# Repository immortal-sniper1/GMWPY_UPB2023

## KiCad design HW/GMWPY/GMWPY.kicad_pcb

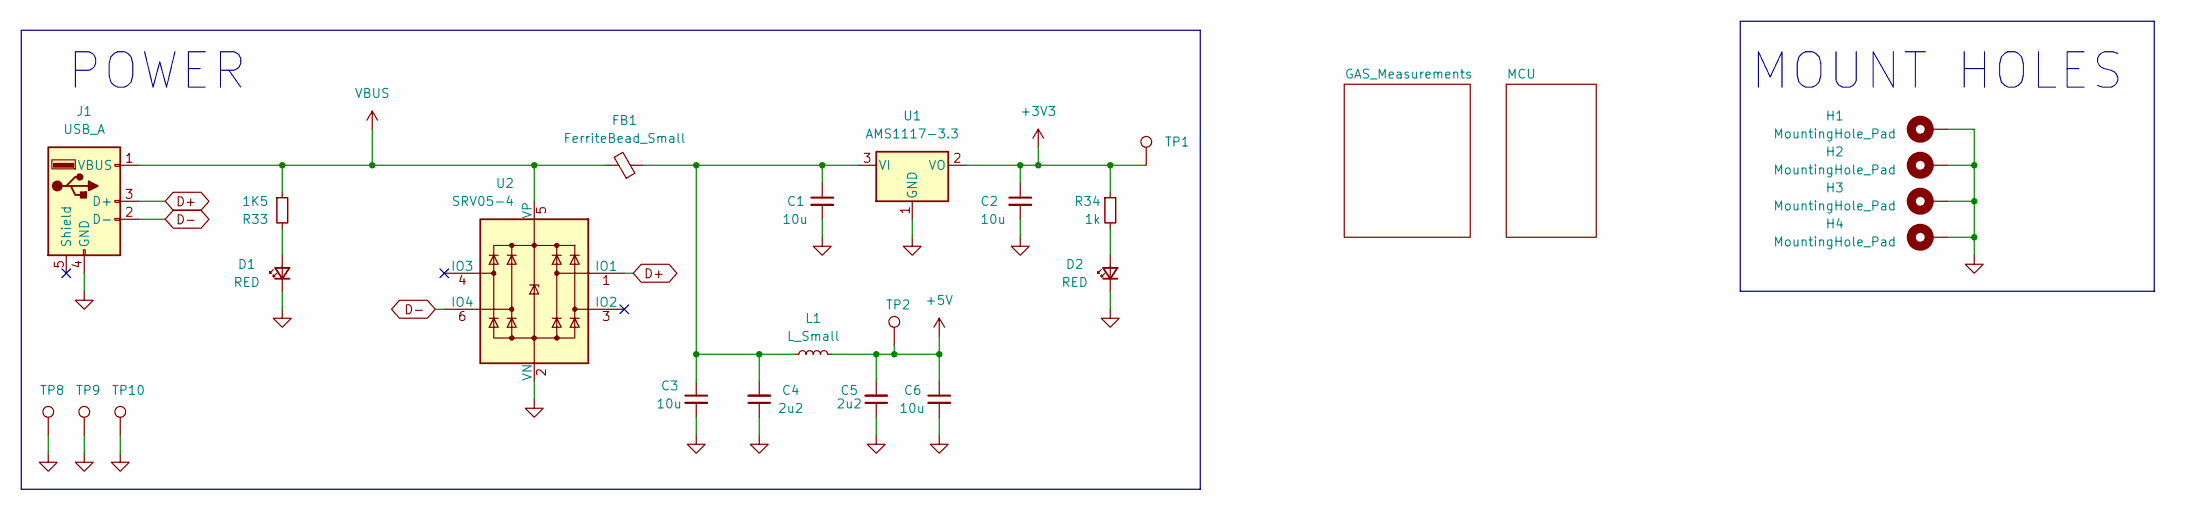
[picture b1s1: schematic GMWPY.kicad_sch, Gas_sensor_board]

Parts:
C1, C2, C3, C6: 10u; C_0805_2012Metric; LCSC C15850
C4, C5: 2u2; C_0603_1608Metric; LCSC C23630
D1, D2: RED; LED_0603_1608Metric; LCSC C2286
FB1: FerriteBead_Small; L_0805_2012Metric; LCSC C1015
H1, H2, H3, H4: MountingHole_Pad; MountingHole_3.2mm_M3_DIN965_Pad_TopBottom
J1: USB_A; USB1040GFLB
L1: L_Small; L_0603_1608Metric; LCSC C13415
R33: 1K5; R_0603_1608Metric; LCSC C22843
R34: 1k; R_0603_1608Metric; LCSC C21190
TP1, TP2, TP8, TP9, TP10: TestPoint; TestPoint_Pad_1.5x1.5mm
U1: AMS1117-3.3; SOT-223-3_TabPin2; LCSC C6186
U2: SRV05-4; SOT-23-6; LCSC C85364

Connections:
+3V3: C2.1, R34.1, TP1.1, U1.2 (VO); also elsewhere on the board
+5V: C5.2, C6.1, L1.2, TP2.1; also elsewhere on the board
D+: J1.3 (D+), U2.1 (IO1); also elsewhere on the board
D-: J1.2 (D-), U2.6 (IO4); also elsewhere on the board
GND: C1.2, C2.2, C3.2, C4.1, C5.1, C6.2, D1.1 (K), D2.1 (K), H1.1, H2.1, H3.1, H4.1, J1.4 (GND), TP8.1, TP9.1, TP10.1, U1.1 (GND), U2.2 (VN); also elsewhere on the board
unnamed: C1.1, C3.1, C4.2, FB1.1, L1.1, U1.3 (VI)
unnamed: D1.2 (A), R33.2
unnamed: D2.2 (A), R34.2
VBUS: FB1.2, J1.1 (VBUS), R33.1, U2.5 (VP); also elsewhere on the board

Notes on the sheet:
POWER
MOUNT HOLES

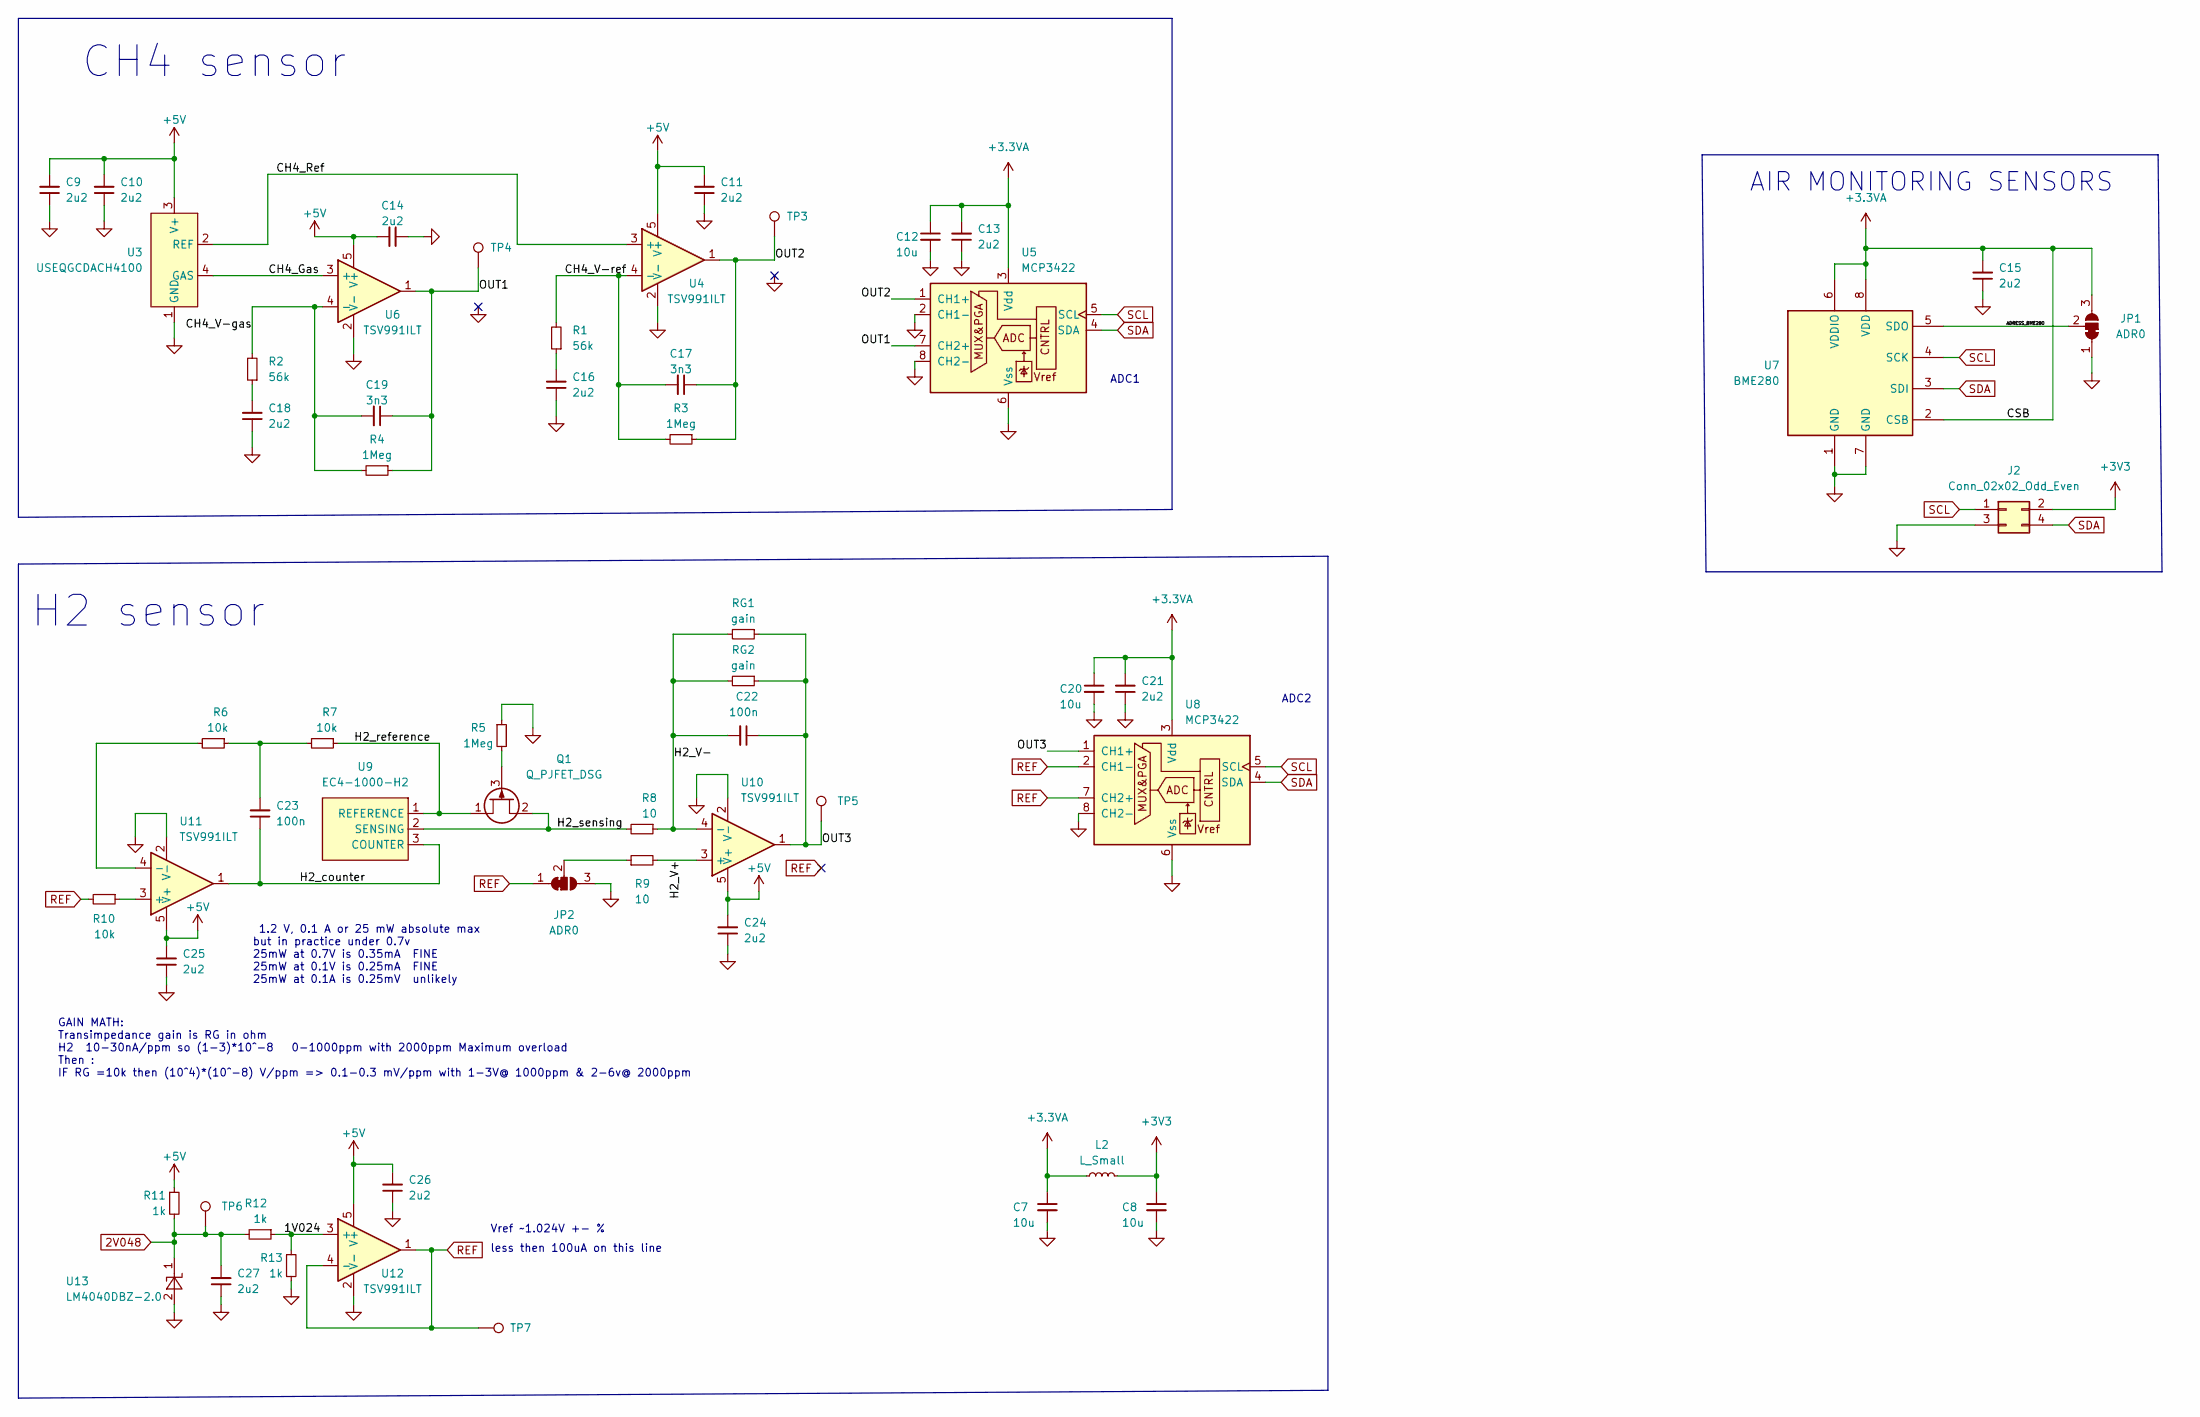
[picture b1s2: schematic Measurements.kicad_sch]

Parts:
C7, C8, C12, C20: 10u; C_0805_2012Metric; LCSC C15850
C9, C10, C11, C13, C14, C15, C16, C18, C21, C24, C25, C26, C27: 2u2; C_0603_1608Metric; LCSC C23630
C17, C19: 3n3; C_0603_1608Metric; LCSC C1613
C22, C23: 100n; C_0603_1608Metric; LCSC C14663
J2: Conn_02x02_Odd_Even; PinHeader_2x02_P2.54mm_Vertical
JP1, JP2: ADR0; SolderJumper-3_P1.3mm_Bridged12_RoundedPad1.0x1.5mm_NumberL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
L2: L_Small; L_0603_1608Metric; LCSC C13415
Q1: Q_PJFET_DSG; SOT-23; LCSC C106763
R1, R2: 56k; R_0603_1608Metric; LCSC C23206
R3, R4, R5: 1Meg; R_0603_1608Metric; LCSC C22935
R6, R7, R10: 10k; R_0603_1608Metric; LCSC C25804
R8, R9: 10; R_0603_1608Metric; LCSC C22859
R11, R12, R13: 1k; R_0603_1608Metric; LCSC C21190
RG1: gain; R_0603_1608Metric; LCSC x
RG2: gain; R_0603_1608Metric; LCSC C25804
TP3, TP4, TP5, TP6, TP7: TestPoint; TestPoint_Pad_1.5x1.5mm
U3: USEQGCDACH4100; KEMET-4-PIN-GAS-SENSOR; MOUSER 80-USEQGCDACH4100
U4, U6, U10, U11, U12: TSV991ILT; SOT-23-5_HandSoldering; LCSC C157443
U5, U8: MCP3422; SOIC-8_3.9x4.9mm_P1.27mm
U7: BME280; Bosch_LGA-8_2.5x2.5mm_P0.65mm_ClockwisePinNumbering
U9: EC4-1000-H2; EC4-3pin; MOUSER 523-EC4-1000-H2
U13: LM4040DBZ-2.0; SOT-23; LCSC C431732

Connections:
2V048: C27.2, R11.2, R12.2, TP6.1, U13.1 (K)
+3.3VA: C7.1, C12.1, C13.2, C15.2, C20.1, C21.2, JP1.3 (B), L2.1, U5.3 (Vdd), U7.2 (CSB), U7.6 (VDDIO), U7.8 (VDD), U8.3 (Vdd)
+3V3: C8.1, J2.2, L2.2; also elsewhere on the board
+5V: C9.2, C10.2, C11.2, C14.2, C24.2, C25.2, C26.2, R11.1, U3.3 (V+), U4.5 (V+), U6.5 (V+), U10.5 (V+), U11.5 (V+), U12.5 (V+); also elsewhere on the board
/GAS_Measurements/1V024: R12.1, R13.1, U12.3 (+)
/GAS_Measurements/ADRESS_BME280: JP1.2 (C), U7.5 (SDO)
/GAS_Measurements/CH4_Gas: U3.4 (GAS), U6.3 (+)
/GAS_Measurements/CH4_Ref: U3.2 (REF), U4.3 (+)
/GAS_Measurements/CH4_V-gas: C19.2, R2.2, R4.2, U6.4 (-)
/GAS_Measurements/CH4_V-ref: C17.2, R1.2, R3.2, U4.4 (-)
/GAS_Measurements/H2_V+: R9.2, U10.3 (+)
/GAS_Measurements/H2_V-: C22.2, R8.1, RG1.2, RG2.2, U10.4 (-)
/GAS_Measurements/H2_counter: C23.1, U9.3 (COUNTER), U11.1
/GAS_Measurements/H2_reference: Q1.1 (D), R7.1, U9.1 (REFERENCE)
/GAS_Measurements/H2_sensing: Q1.2 (S), R8.2, U9.2 (SENSING)
/GAS_Measurements/OUT1: C19.1, R4.1, TP4.1, U5.7 (CH2+), U6.1
/GAS_Measurements/OUT2: C17.1, R3.1, TP3.1, U4.1, U5.1 (CH1+)
/GAS_Measurements/OUT3: C22.1, RG1.1, RG2.1, TP5.1, U8.1 (CH1+), U10.1
GND: C7.2, C8.2, C9.1, C10.1, C11.1, C12.2, C13.1, C14.1, C15.1, C16.1, C18.1, C20.2, C21.1, C24.1, C25.1, C26.1, C27.1, J2.3, JP1.1 (A), JP2.3 (B), R5.1, R13.2, U3.1 (GND), U4.2 (V-), U5.2 (CH1-), U5.6 (Vss), U5.8 (CH2-), U6.2 (V-), U7.1 (GND), U7.7 (GND), U8.6 (Vss), U8.8 (CH2-), U10.2 (V-), U11.2 (V-), U12.2 (V-), U13.2 (A); also elsewhere on the board
GPIO_5: J2.1, U5.5 (SCL), U7.4 (SCK), U8.5 (SCL); also elsewhere on the board
GPIO_6: J2.4, U5.4 (SDA), U7.3 (SDI), U8.4 (SDA); also elsewhere on the board
unnamed: C16.2, R1.1
unnamed: C18.2, R2.1
unnamed: C23.2, R6.1, R7.2
unnamed: JP2.2 (C), R9.1
unnamed: Q1.3 (G), R5.2
unnamed: R6.2, U11.4 (-)
unnamed: R10.1, U11.3 (+)
REF: JP2.1 (A), R10.2, TP7.1, U8.2 (CH1-), U8.7 (CH2+), U12.1, U12.4 (-)

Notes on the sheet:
GAIN MATH: Transimpedance gain is RG in ohm H2 10-30nA/ppm so (1-3)*10^-8 0-1000ppm with 2000ppm Maximum overload Then : IF RG =10k then (10^4)*(10^-8) V/ppm => 0.1-0.3 mV/ppm with 1-3V@ 1000ppm & 2-6v@ 2000ppm
Vref ~1.024V +- %
AIR MONITORING SENSORS
ADC1
less then 100uA on this line
CH4 sensor
1.2 V, 0.1 A or 25 mW absolute max but in practice under 0.7v 25mW at 0.7V is 0.35mA FINE 25mW at 0.1V is 0.25mA FINE 25mW at 0.1A is 0.25mV unlikely
H2 sensor
ADC2

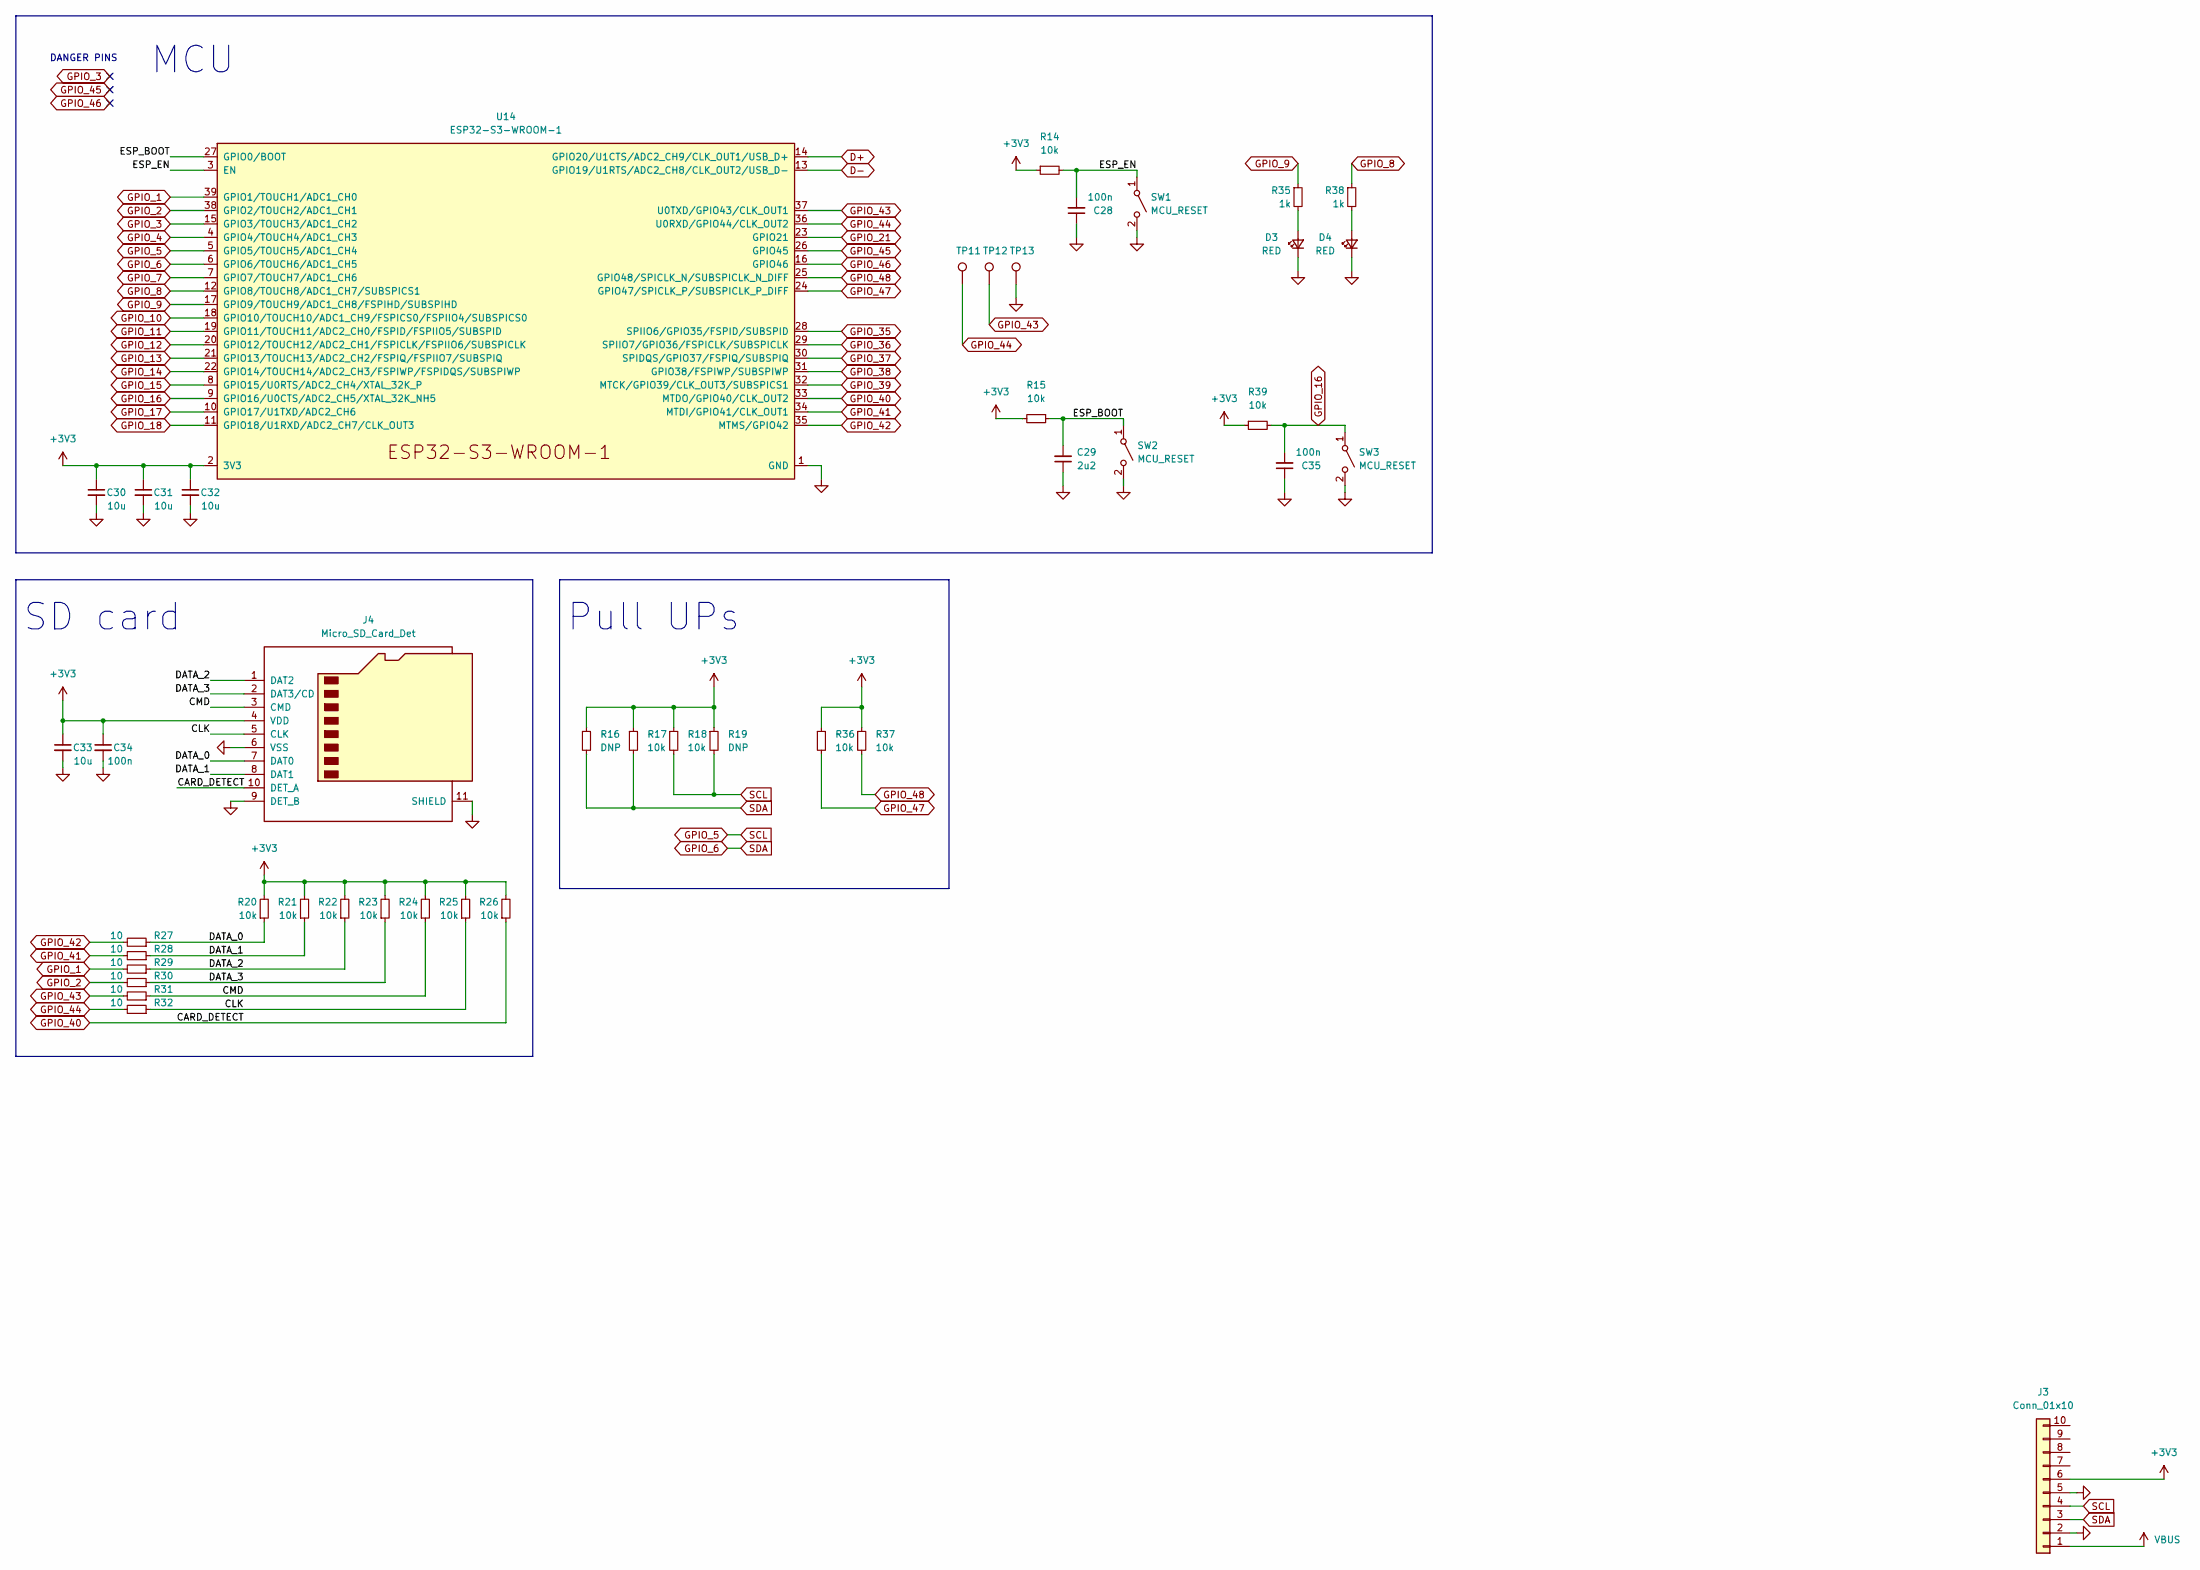
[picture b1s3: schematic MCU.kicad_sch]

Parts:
C28, C34, C35: 100n; C_0603_1608Metric_Pad1.08x0.95mm_HandSolder; LCSC C14663
C29: 2u2; C_0603_1608Metric; LCSC C23630
C30, C31, C32, C33: 10u; C_0805_2012Metric; LCSC C15850
D3, D4: RED; LED_0603_1608Metric; LCSC C2286
J3: Conn_01x10; PinHeader_1x06_P2.54mm_Vertical
J4: Micro_SD_Card_Det; microSD_HC_Molex_104031-0811; LCSC C585350
R14, R15, R17, R18, R36, R37, R39: 10k; R_0603_1608Metric_Pad0.98x0.95mm_HandSolder; LCSC C25804
R16, R19: DNP; R_0603_1608Metric_Pad0.98x0.95mm_HandSolder
R20, R21, R22, R23, R24, R25, R26: 10k; R_0402_1005Metric; LCSC C25744
R27, R28, R29, R30, R31, R32: 10; R_0402_1005Metric; LCSC C25077
R35, R38: 1k; R_0603_1608Metric; LCSC C21190
SW1, SW2, SW3: MCU_RESET; PTS526SK15SMTR2LFS; LCSC C318884
TP11, TP12, TP13: TestPoint; TestPoint_Pad_1.5x1.5mm
U14: ESP32-S3-WROOM-1; LCSC C2913204

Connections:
+3V3: C30.1, C31.1, C32.1, C33.1, C34.1, J3.6, J4.4 (VDD), R14.1, R15.2, R16.1, R17.1, R18.1, R19.1, R20.2, R21.2, R22.2, R23.2, R24.2, R25.2, R26.2, R36.1, R37.1, R39.1, U14.2 (3V3); also elsewhere on the board
/MCU/CLK: J4.5 (CLK), R25.1, R32.1
/MCU/CMD: J4.3 (CMD), R24.1, R31.1
/MCU/DATA_0: J4.7 (DAT0), R20.1, R27.1
/MCU/DATA_1: J4.8 (DAT1), R21.1, R28.1
/MCU/DATA_2: J4.1 (DAT2), R22.1, R29.1
/MCU/DATA_3: J4.2 (DAT3/CD), R23.1, R30.1
/MCU/ESP_BOOT: C29.2, R15.1, SW2.1 (A), U14.27 (GPIO0/BOOT)
/MCU/ESP_EN: C28.2, R14.2, SW1.1 (A), U14.3 (EN)
D+: U14.14 (GPIO20/U1CTS/ADC2_CH9/CLK_OUT1/USB_D+); also elsewhere on the board
D-: U14.13 (GPIO19/U1RTS/ADC2_CH8/CLK_OUT2/USB_D-); also elsewhere on the board
GND: C28.1, C29.1, C30.2, C31.2, C32.2, C33.2, C34.2, C35.1, D3.1 (K), D4.1 (K), J3.2, J3.5, J4.6 (VSS), J4.9 (DET_B), J4.11 (SHIELD), SW1.2 (B), SW2.2 (B), SW3.2 (B), TP13.1, U14.1 (GND), U14.40 (GND), U14.41 (GND); also elsewhere on the board
GPIO_1: R29.2, U14.39 (GPIO1/TOUCH1/ADC1_CH0)
GPIO_2: R30.2, U14.38 (GPIO2/TOUCH2/ADC1_CH1)
GPIO_3: U14.15 (GPIO3/TOUCH3/ADC1_CH2)
GPIO_4: U14.4 (GPIO4/TOUCH4/ADC1_CH3)
GPIO_5: J3.4, R18.2, R19.2, U14.5 (GPIO5/TOUCH5/ADC1_CH4); also elsewhere on the board
GPIO_6: J3.3, R16.2, R17.2, U14.6 (GPIO6/TOUCH6/ADC1_CH5); also elsewhere on the board
GPIO_7: U14.7 (GPIO7/TOUCH7/ADC1_CH6)
GPIO_8: R38.1, U14.12 (GPIO8/TOUCH8/ADC1_CH7/SUBSPICS1)
GPIO_9: R35.1, U14.17 (GPIO9/TOUCH9/ADC1_CH8/FSPIHD/SUBSPIHD)
GPIO_10: U14.18 (GPIO10/TOUCH10/ADC1_CH9/FSPICS0/FSPIIO4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)
GPIO_11: U14.19 (GPIO11/TOUCH11/ADC2_CH0/FSPID/FSPIIO5/S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)
GPIO_12: U14.20 (GPIO12/TOUCH12/ADC2_CH1/FSPICLK/FSPIIO6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)
GPIO_13: U14.21 (GPIO13/TOUCH13/ADC2_CH2/FSPIQ/FSPIIO7/S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)
GPIO_14: U14.22 (GPIO14/TOUCH14/ADC2_CH3/FSPIWP/FSPIDQS/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)
GPIO_15: U14.8 (GPIO15/U0RTS/ADC2_CH4/XTAL_32K_P)
GPIO_16: C35.2, R39.2, SW3.1 (A), U14.9 (GPIO16/U0CTS/ADC2_CH5/XTAL_32K_NH5)
GPIO_17: U14.10 (GPIO17/U1TXD/ADC2_CH6)
GPIO_18: U14.11 (GPIO18/U1RXD/ADC2_CH7/CLK_OUT3)
GPIO_21: U14.23 (GPIO21)
GPIO_35: U14.28 (SPIIO6/GPIO35/FSPID/SUBSPID)
GPIO_36: U14.29 (SPIIO7/GPIO36/FSPICLK/SUBSPICLK)
GPIO_37: U14.30 (SPIDQS/GPIO37/FSPIQ/SUBSPIQ)
GPIO_38: U14.31 (GPIO38/FSPIWP/SUBSPIWP)
GPIO_39: U14.32 (MTCK/GPIO39/CLK_OUT3/SUBSPICS1)
GPIO_40: J4.10 (DET_A), R26.1, U14.33 (MTDO/GPIO40/CLK_OUT2)
GPIO_41: R28.2, U14.34 (MTDI/GPIO41/CLK_OUT1)
GPIO_42: R27.2, U14.35 (MTMS/GPIO42)
GPIO_43: R31.2, TP12.1, U14.37 (U0TXD/GPIO43/CLK_OUT1)
GPIO_44: R32.2, TP11.1, U14.36 (U0RXD/GPIO44/CLK_OUT2)
GPIO_45: U14.26 (GPIO45)
GPIO_46: U14.16 (GPIO46)
GPIO_47: R36.2, U14.24 (GPIO47/SPICLK_P/SUBSPICLK_P_DIFF)
GPIO_48: R37.2, U14.25 (GPIO48/SPICLK_N/SUBSPICLK_N_DIFF)
unnamed: D3.2 (A), R35.2
unnamed: D4.2 (A), R38.2
VBUS: J3.1; also elsewhere on the board

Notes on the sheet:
Pull UPs
DANGER PINS
MCU
SD card

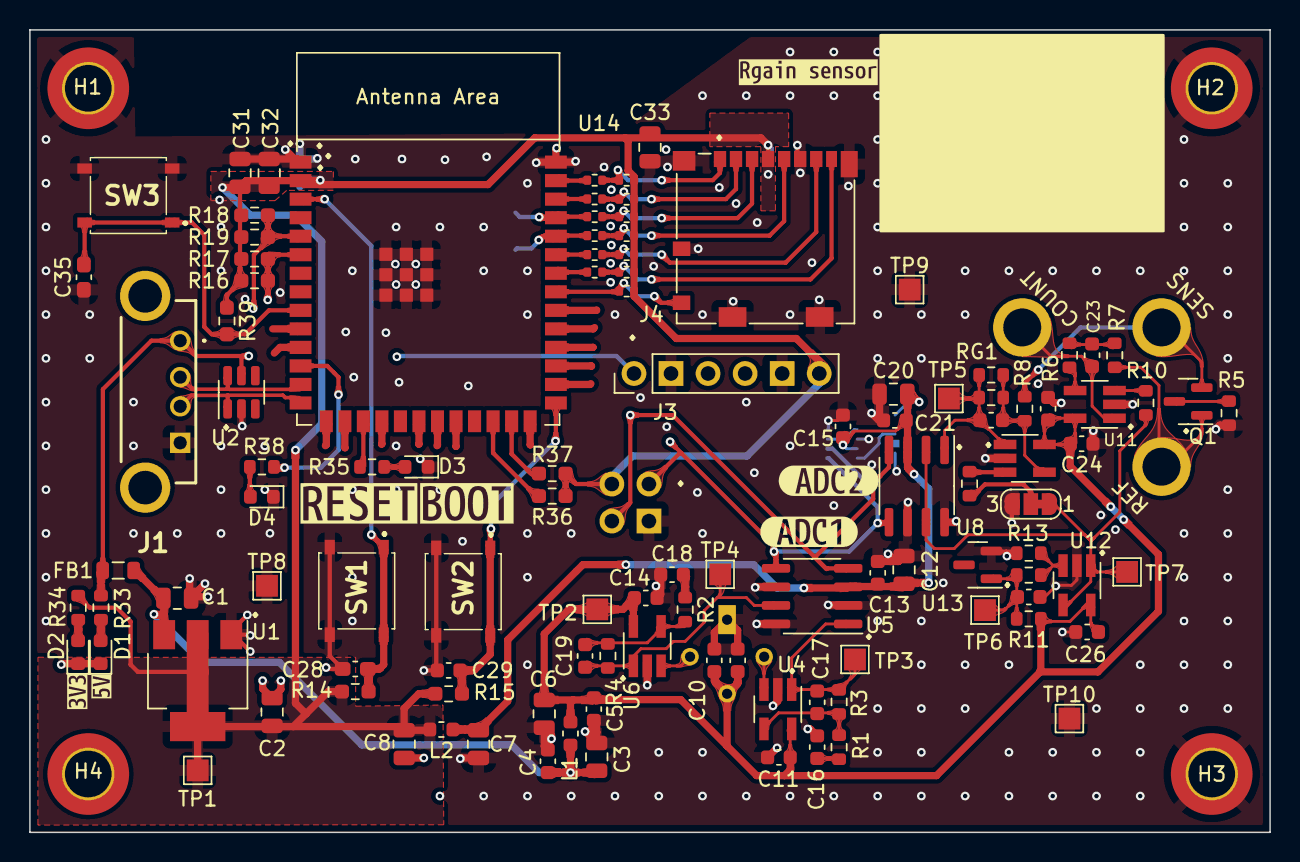
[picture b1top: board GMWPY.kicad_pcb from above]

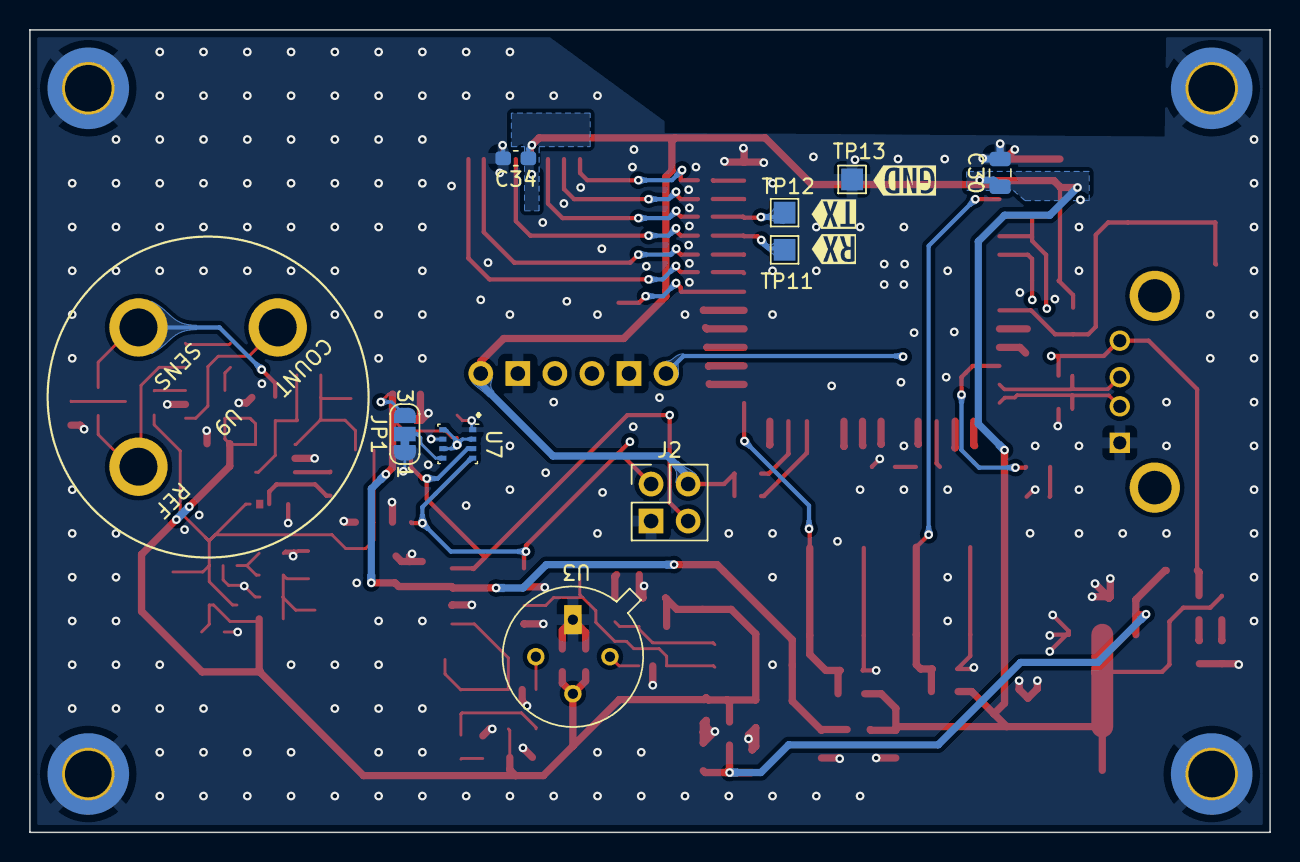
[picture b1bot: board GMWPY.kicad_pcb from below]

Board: 4 copper layers, 85.0 x 55.0 mm, 134 parts (13 on the bottom side), 57 nets.

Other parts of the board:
kibuzzard-6406DECD: G***; kibuzzard-6406DECD
kibuzzard-6406DEDF: G***; kibuzzard-6406DEDF
kibuzzard-6406E44E: G***; kibuzzard-6406E44E
kibuzzard-6406E441: G***; kibuzzard-6406E441
kibuzzard-640733B2: G***; kibuzzard-640733B2
kibuzzard-640843D3: G***; kibuzzard-640843D3
kibuzzard-640843E2: G***; kibuzzard-640843E2
kibuzzard-642169AB: G***; kibuzzard-642169AB
kibuzzard-642169BA: G***; kibuzzard-642169BA
kibuzzard-642169F1: G***; kibuzzard-642169F1

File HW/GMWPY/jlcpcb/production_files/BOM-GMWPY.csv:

Comment,Designator,Footprint,LCSC
FerriteBead_Small,FB1,L_0805_2012Metric,C1015
Q_PJFET_DSG,Q1,SOT-23,C106763
L_Small,"L1,L2",L_0603_1608Metric,C13415
100n,"C22,C23,C28,C34,C35",C_0603_1608Metric,C14663
TSV991ILT,"U10,U11,U12,U4,U6",SOT-23-5_HandSoldering,C157443
10u,"C1,C12,C2,C20,C3,C30,C31,C32,C33,C6,C7,C8",C_0805_2012Metric,C15850
3n3,"C17,C19",C_0603_1608Metric,C1613
1k,"R11,R12,R13,R34,R35,R38",R_0603_1608Metric,C21190
1K5,R33,R_0603_1608Metric,C22843
10,"R8,R9",R_0603_1608Metric,C22859
RED,"D1,D2,D3,D4",LED_0603_1608Metric,C2286
1Meg,"R3,R4,R5",R_0603_1608Metric,C22935
56k,"R1,R2",R_0603_1608Metric,C23206
2u2,"C10,C11,C13,C14,C15,C16,C18,C21,C24,C25,C26,C27,C29,C4,C5,C9",C_0603_1608Metric,C23630
10,"R27,R28,R29,R30,R31,R32",R_0402_1005Metric,C25077
10k,"R20,R21,R22,R23,R24,R25,R26",R_0402_1005Metric,C25744
10k,"R10,R14,R15,R17,R18,R36,R37,R39,R6,R7,RG2",R_0603_1608Metric,C25804
ESP32-S3-WROOM-1,U14,ESP32-S3-WROOM-1,C2913204
MCU_RESET,"SW1,SW2,SW3",PTS526SK15SMTR2LFS,C318884
LM4040DBZ-2.0,U13,SOT-23,C431732
Micro_SD_Card_Det,J4,microSD_HC_Molex_104031-0811,C585350
AMS1117-3.3,U1,SOT-223-3_TabPin2,C6186
SRV05-4,U2,SOT-23-6,C85364
USB_A,J1,USB1040GFLB,
MCP3422,U8,SOIC-8_3.9x4.9mm_P1.27mm,
gain,RG1,R_0603_1608Metric,
MCP3422,U5,SOIC-8_3.9x4.9mm_P1.27mm,
BME280,U7,Bosch_LGA-8_2.5x2.5mm_P0.65mm_ClockwisePinNumbering,
EC4-1000-H2,U9,EC4-3pin,
USEQGCDACH4100,U3,KEMET-4-PIN-GAS-SENSOR,

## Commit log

2023-05-09 Added .gitignore
2023-05-09 Added working ADC read
2023-05-15 Cleanup
